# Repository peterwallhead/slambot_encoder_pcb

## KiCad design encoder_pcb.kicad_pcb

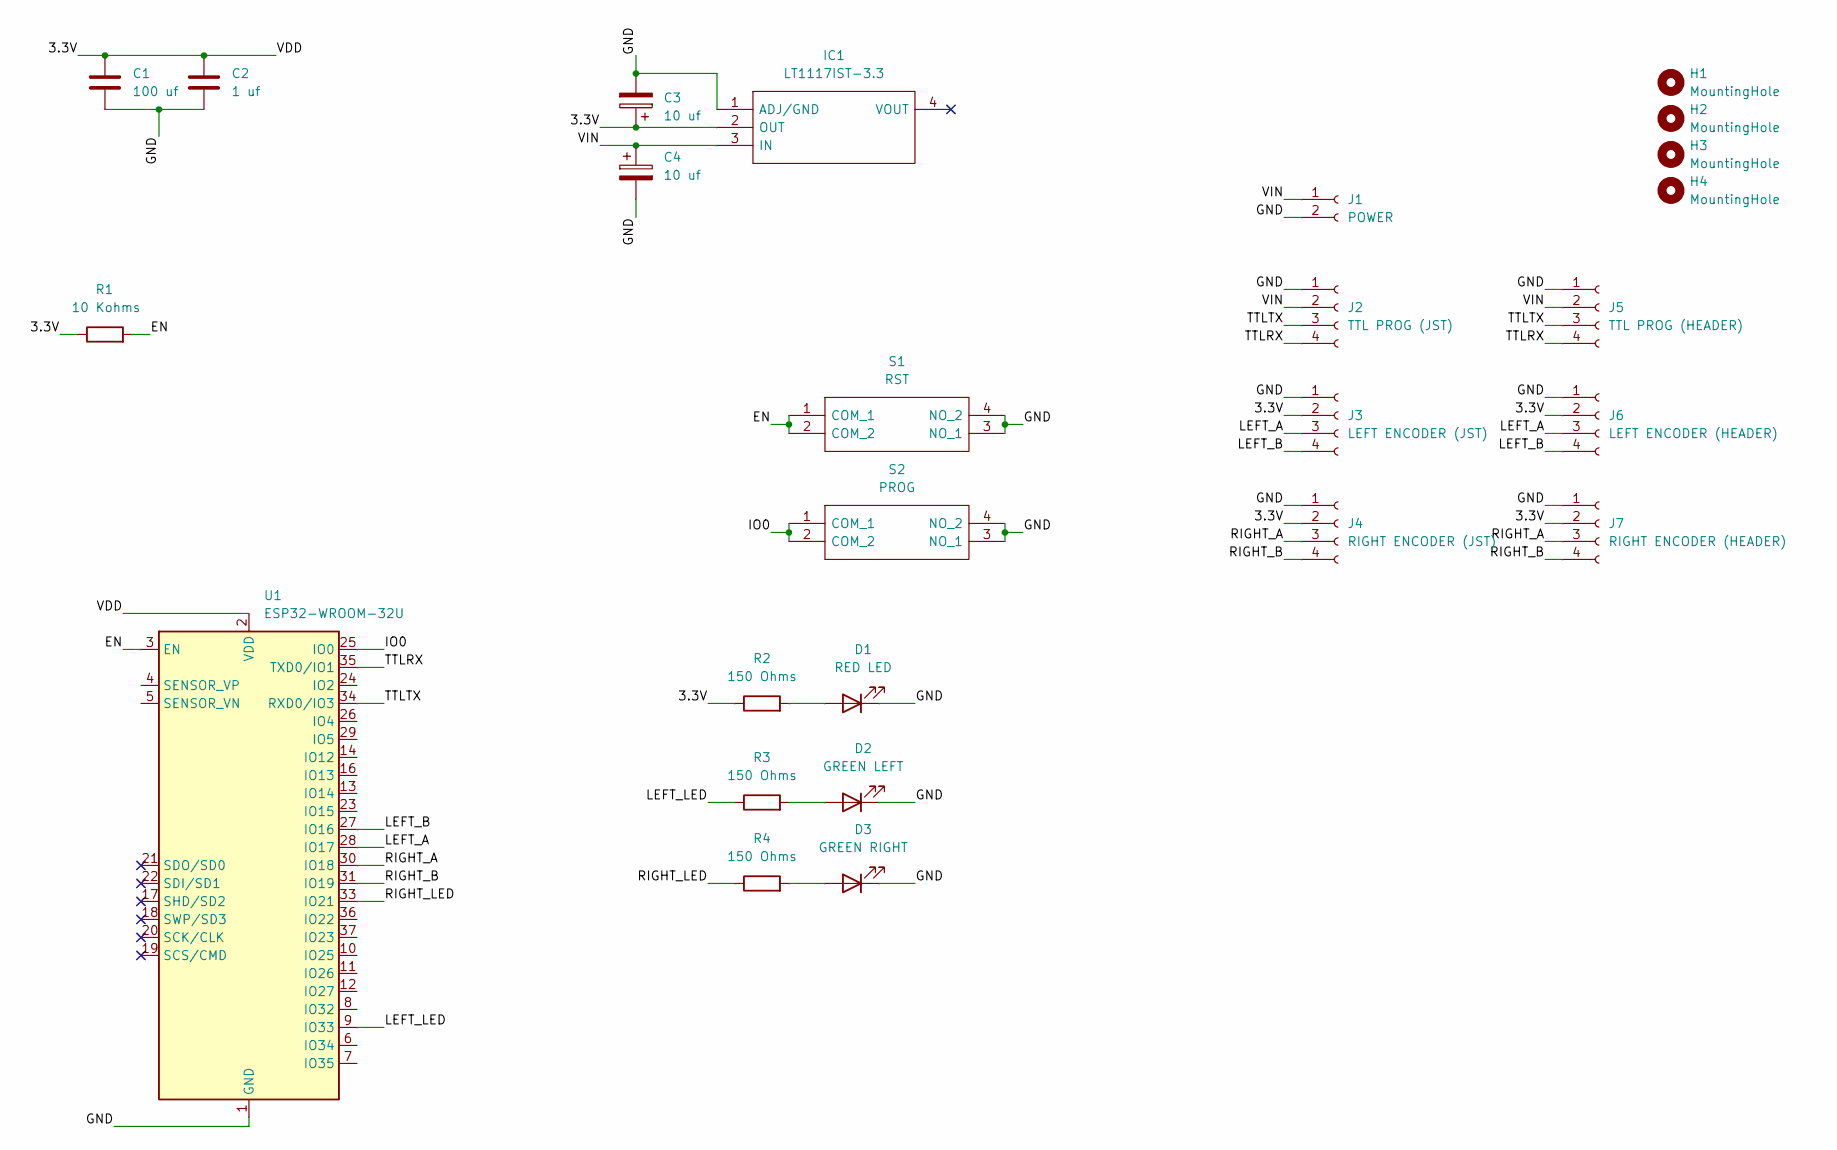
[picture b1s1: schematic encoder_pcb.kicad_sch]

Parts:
C1: 100 uf; C_1206_3216Metric_Pad1.33x1.80mm_HandSolder
C2: 1 uf; C_1206_3216Metric_Pad1.33x1.80mm_HandSolder
C3, C4: 10 uf; CP_EIA-3216-10_Kemet-I_Pad1.58x1.35mm_HandSolder
D1: RED LED; LED_1206_3216Metric_Pad1.42x1.75mm_HandSolder
D2: GREEN LEFT; LED_1206_3216Metric_Pad1.42x1.75mm_HandSolder
D3: GREEN RIGHT; LED_1206_3216Metric_Pad1.42x1.75mm_HandSolder
H1, H2, H3, H4: MountingHole; MountingHole_3.2mm_M3
IC1: LT1117IST-3.3; SOT230P700X180-4N; Manufacturer_Part_Number LT1117IST-3.3#PBF; Mouser Part Number 584-LT1117IST-3.3PBF
J1: POWER; Term_Block_1x2_P5.08MM
J2: TTL PROG (JST); JST_XH_B4B-XH-A_1x04_P2.50mm_Vertical
J3: LEFT ENCODER (JST); JST_XH_B4B-XH-A_1x04_P2.50mm_Vertical
J4: RIGHT ENCODER (JST); JST_XH_B4B-XH-A_1x04_P2.50mm_Vertical
J5: TTL PROG (HEADER); PinHeader_1x04_P2.54mm_Vertical
J6: LEFT ENCODER (HEADER); PinSocket_1x04_P2.54mm_Vertical
J7: RIGHT ENCODER (HEADER); PinSocket_1x04_P2.54mm_Vertical
R1: 10 Kohms; R_1206_3216Metric_Pad1.30x1.75mm_HandSolder
R2, R3, R4: 150 Ohms; R_1206_3216Metric_Pad1.30x1.75mm_HandSolder
S1: RST; Switch_Tactile_THT_6x6mm; Manufacturer_Part_Number DTS-61N-V; Mouser Part Number 113-DTS-61N-V
S2: PROG; Switch_Tactile_THT_6x6mm; Manufacturer_Part_Number DTS-61N-V; Mouser Part Number 113-DTS-61N-V
U1: ESP32-WROOM-32U

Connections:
/3.3V: C1.1, C2.1, C3.1, IC1.2 (OUT), J3.2, J4.2, J6.2, J7.2, R1.1, R2.1, U1.2 (VDD)
/EN: R1.2, S1.1 (COM_1), S1.2 (COM_2), U1.3 (EN)
/GND: C1.2, C2.2, C3.2, C4.2, D1.1 (K), D2.1 (K), D3.1 (K), IC1.1 (ADJ/GND), J1.2, J2.1, J3.1, J4.1, J5.1, J6.1, J7.1, S1.3 (NO_1), S1.4 (NO_2), S2.3 (NO_1), S2.4 (NO_2), U1.1 (GND), U1.15 (GND), U1.38 (GND), U1.39 (GND)
/IO0: S2.1 (COM_1), S2.2 (COM_2), U1.25 (IO0)
/LEFT_A: J3.3, J6.3, U1.28 (IO17)
/LEFT_B: J3.4, J6.4, U1.27 (IO16)
/LEFT_LED: R3.1, U1.9 (IO33)
/RIGHT_A: J4.3, J7.3, U1.30 (IO18)
/RIGHT_B: J4.4, J7.4, U1.31 (IO19)
/RIGHT_LED: R4.1, U1.33 (IO21)
/TTLRX: J2.4, J5.4, U1.35 (TXD0/IO1)
/TTLTX: J2.3, J5.3, U1.34 (RXD0/IO3)
/VIN: C4.1, IC1.3 (IN), J1.1, J2.2, J5.2
unnamed: D1.2 (A), R2.2
unnamed: D2.2 (A), R3.2
unnamed: D3.2 (A), R4.2

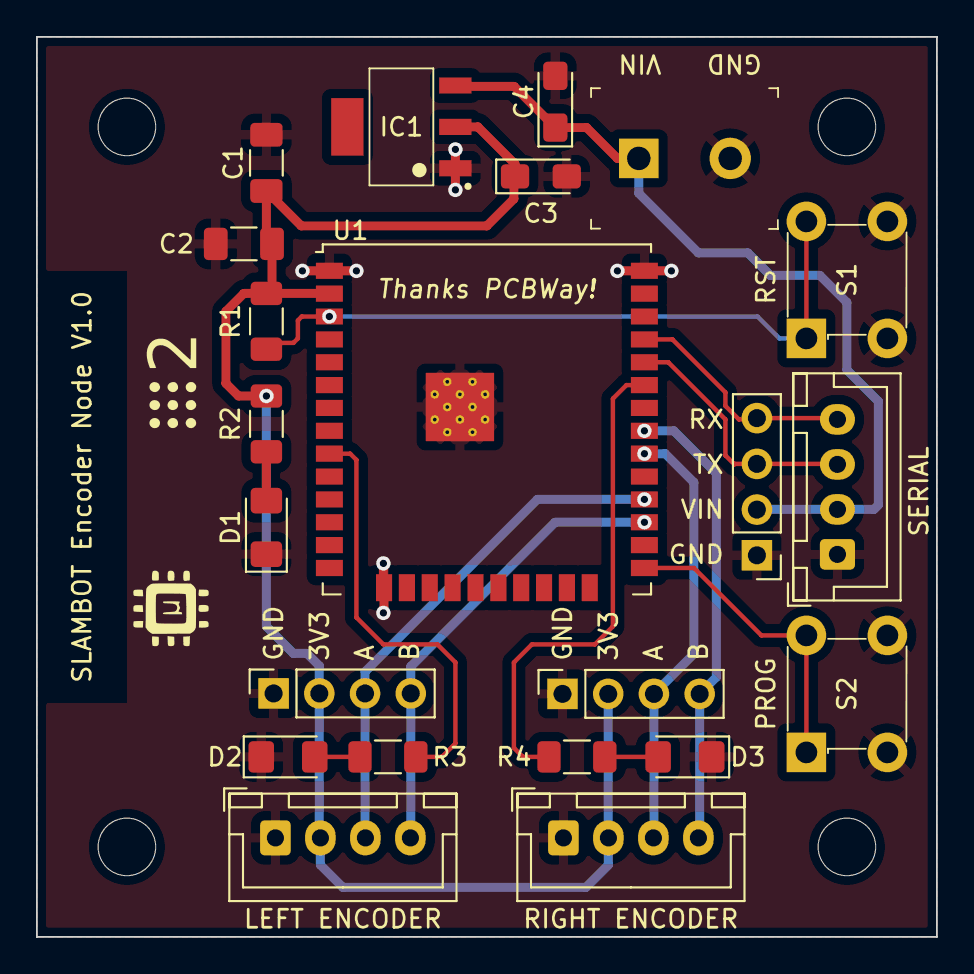
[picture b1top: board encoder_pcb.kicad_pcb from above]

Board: 2 copper layers, 50.0 x 50.0 mm, 26 parts (0 on the bottom side), 16 nets.

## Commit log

2025-05-23 First board print run
2025-05-25 Correct C2 value

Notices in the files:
encoder_pcb.kicad_pcb:
Copyright (c) 2025 Peter Wallhead
